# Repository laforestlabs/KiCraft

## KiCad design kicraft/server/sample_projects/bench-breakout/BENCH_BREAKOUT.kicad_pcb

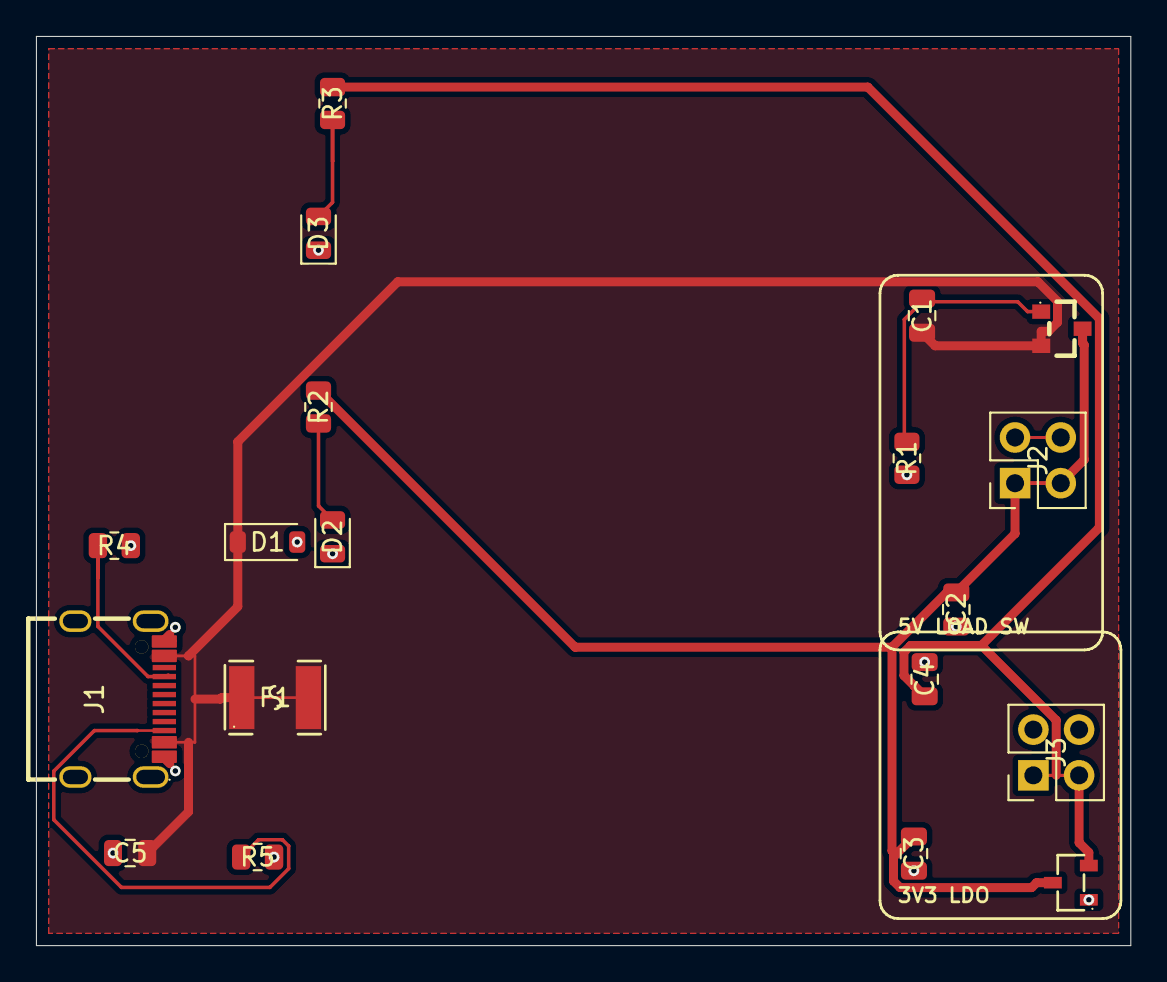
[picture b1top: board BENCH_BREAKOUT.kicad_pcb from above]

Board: 2 copper layers, 60.8 x 50.5 mm, 19 parts (0 on the bottom side), 9 nets.

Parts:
C1: 100nF; C_0805_2012Metric
C2, C5: 10uF; C_0805_2012Metric
C3, C4: 1uF; C_0805_2012Metric
D1: 5V TVS; D_SOD-123
D2: Red; LED_0805_2012Metric
D3: Green; LED_0805_2012Metric
F1: MF-MSMF050-2; F1812
J1: TYPE-C-31-M-12; USB-C_SMD-TYPE-C-31-M-12_1
J2, J3: 2x02 Header; PinHeader_2x02_P2.54mm_Vertical
Q1: AO3401A; SOT-23_L2.9-W1.3-P1.90-LS2.4-BR
R1: 100k; R_0805_2012Metric
R2, R3: 470; R_0805_2012Metric
R4, R5: 5.1k; R_0805_2012Metric
U1: XC6206P332MR; SOT-23-3_L2.9-W1.3-P1.90-LS2.4-BR

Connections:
+3V3: C4.1, J3.1, J3.3, R3.1, U1.2
+5V: C2.1, C3.1, J2.1, J2.3, Q1.3, R2.1, U1.3
CC1: J1.A5, R4.1
CC2: J1.B5, R5.1
GATE: C1.1, Q1.1, R1.1
GND: C2.2, C3.2, C4.2, C5.2, D1.2, D2.1, D3.1, J1.1, J1.2, J1.3, J1.4, J1.A1B12, J1.B1A12, J2.2, J2.4, J3.2, J3.4, R1.2, R4.2, R5.2, U1.1
LED3V3_ANODE: D3.2, R3.2
LED5V_ANODE: D2.2, R2.2
VBUS: C1.2, C5.1, D1.1, F1.1, F1.2, J1.A4B9, J1.B4A9, Q1.2

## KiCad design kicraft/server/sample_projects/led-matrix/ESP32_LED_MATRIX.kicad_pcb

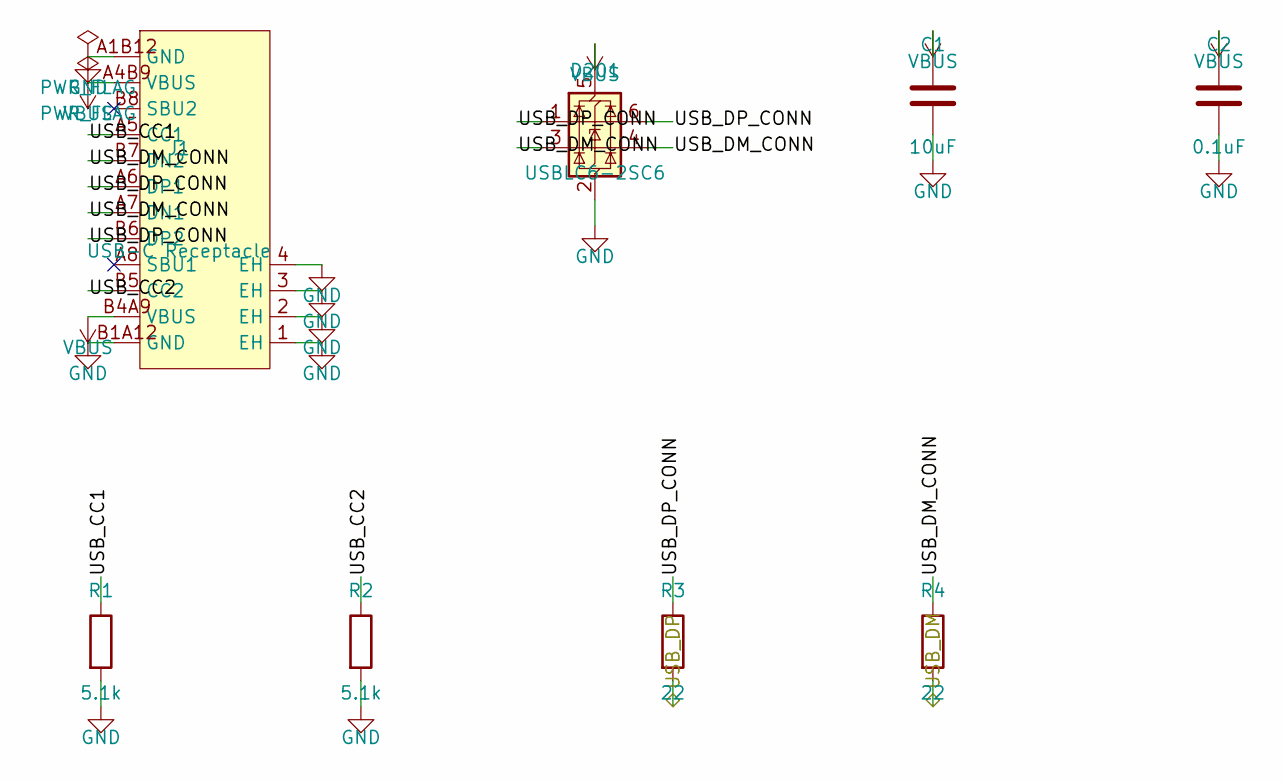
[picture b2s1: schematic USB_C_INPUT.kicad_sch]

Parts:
C1: 10uF; C_0805_2012Metric
C2: 0.1uF; C_0402_1005Metric
D201: USBLC6-2SC6; SOT-23-6
J1: USB-C Receptacle; USB-C_SMD-TYPE-C-31-M-12_1
R1, R2: 5.1k; R_0402_1005Metric
R3, R4: 22; R_0402_1005Metric

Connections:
USB_CC1: J1.A5 (CC1), R1.1
USB_CC2: J1.B5 (CC2), R2.1
USB_DM: R4.2; also elsewhere on the board
USB_DM_CONN: D201.3 (I/O2), D201.4 (I/O2), J1.A7 (DN1), J1.B7 (DN2), R4.1
USB_DP: R3.2; also elsewhere on the board
USB_DP_CONN: D201.1 (I/O1), D201.6 (I/O1), J1.A6 (DP1), J1.B6 (DP2), R3.1

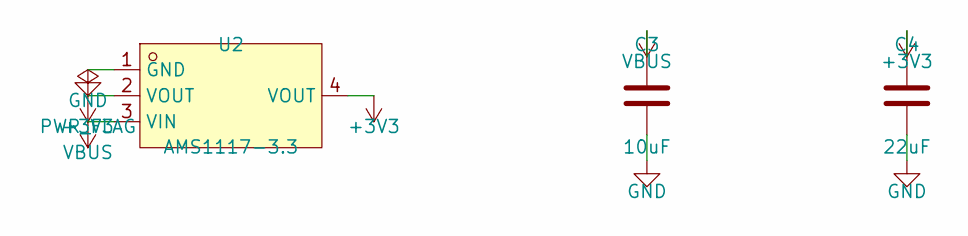
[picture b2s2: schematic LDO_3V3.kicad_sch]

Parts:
C3: 10uF; C_0805_2012Metric
C4: 22uF; C_0805_2012Metric
U2: AMS1117-3.3; SOT-223-3_L6.5-W3.4-P2.30-LS7.0-BR

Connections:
+3V3: C4.1, U2.2 (VOUT), U2.4 (VOUT); also elsewhere on the board

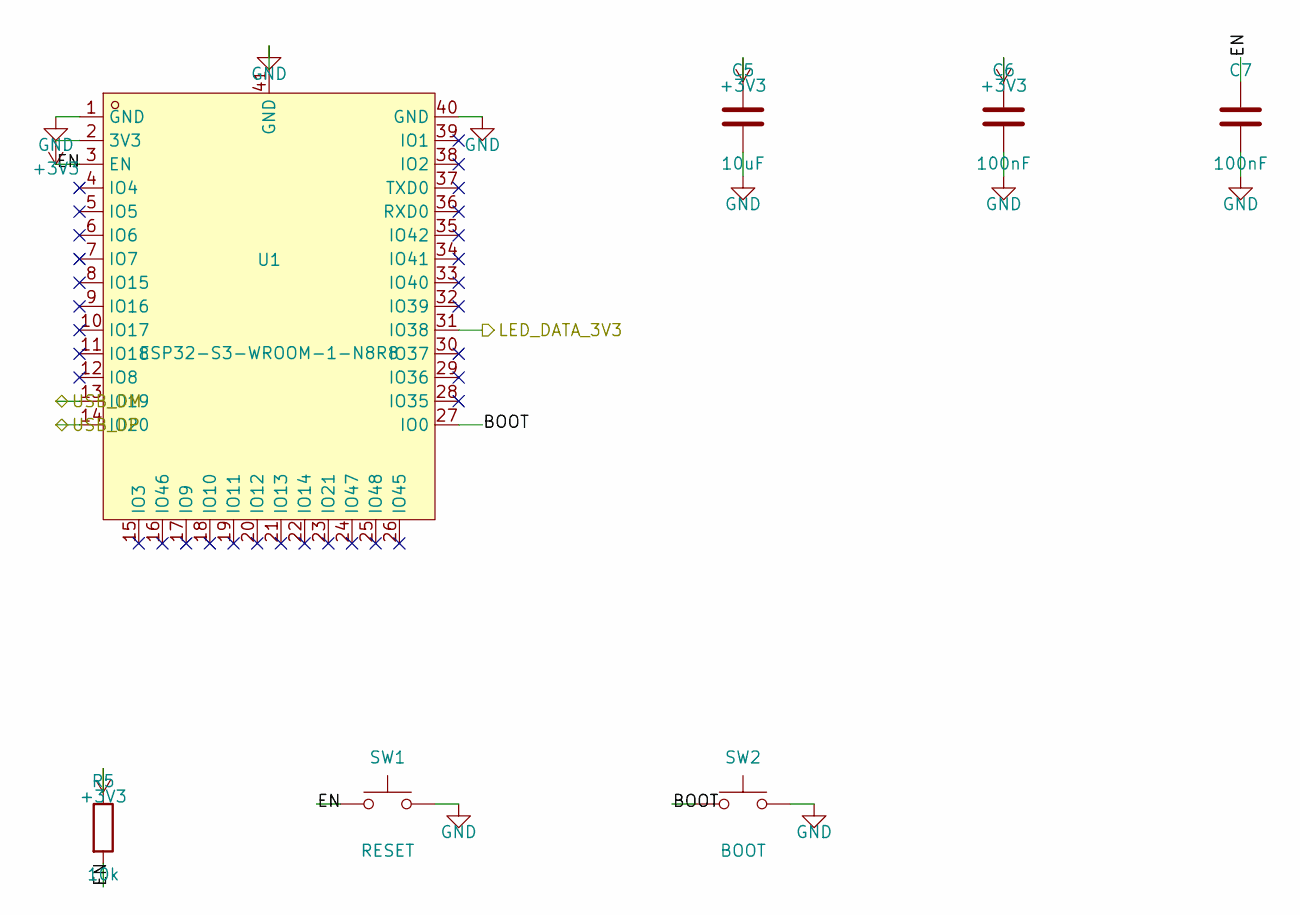
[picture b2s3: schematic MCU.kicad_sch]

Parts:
C5: 10uF; C_0805_2012Metric
C6, C7: 100nF; C_0402_1005Metric
R5: 10k; R_0402_1005Metric
SW1: RESET; SW_Push_1P1T_NO_CK_KMR2
SW2: BOOT; SW_Push_1P1T_NO_CK_KMR2
U1: ESP32-S3-WROOM-1-N8R8; WIRELM-SMD_ESP32-S3-WROOM-1

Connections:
+3V3: C5.1, C6.1, R5.1, U1.2 (3V3); also elsewhere on the board
BOOT: SW2.1, U1.27 (IO0)
EN: C7.1, R5.2, SW1.1, U1.3 (EN)
LED_DATA_3V3: U1.31 (IO38); also elsewhere on the board
USB_DM: U1.13 (IO19); also elsewhere on the board
USB_DP: U1.14 (IO20); also elsewhere on the board

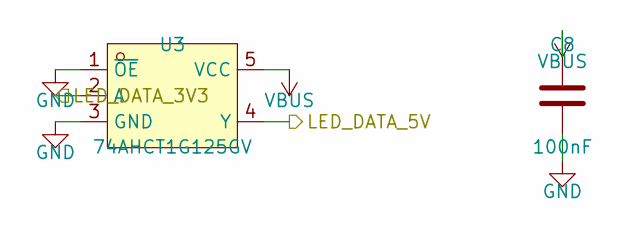
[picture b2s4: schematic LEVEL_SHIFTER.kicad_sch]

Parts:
C8: 100nF; C_0402_1005Metric
U3: 74AHCT1G125GV; SOT-23-5_L3.0-W1.7-P0.95-LS2.8-BL

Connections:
LED_DATA_3V3: U3.2 (A); also elsewhere on the board
LED_DATA_5V: U3.4 (Y); also elsewhere on the board

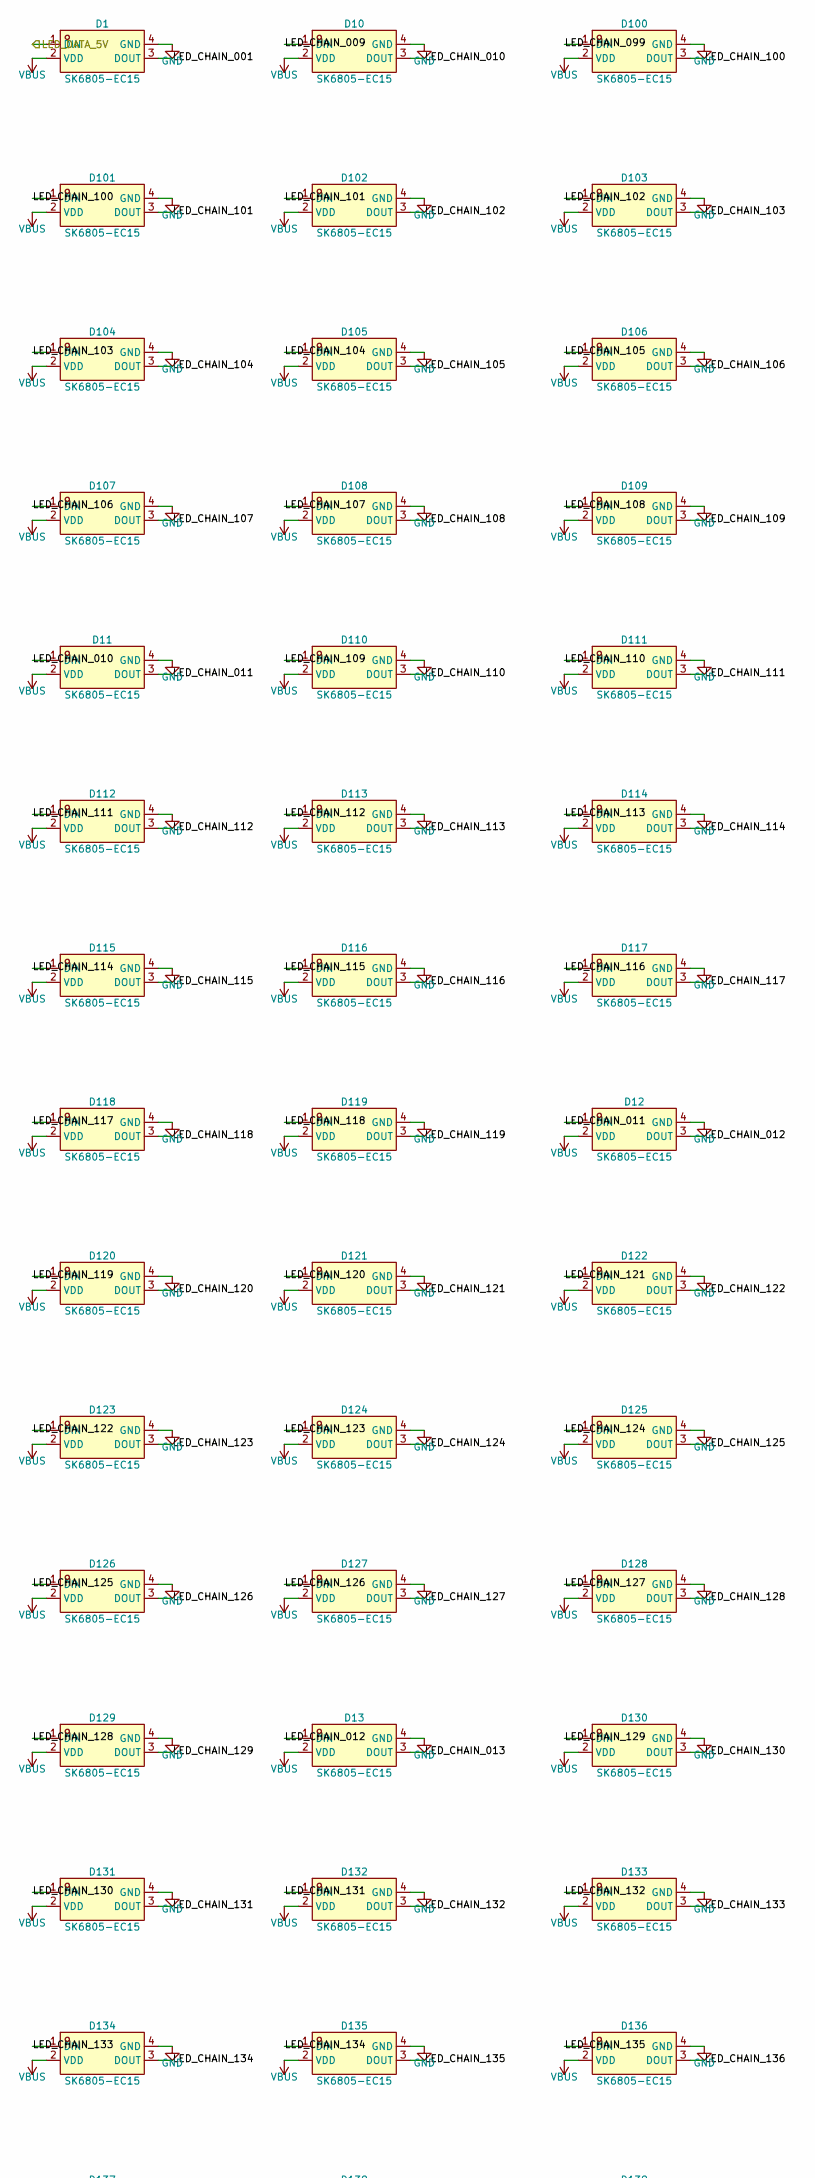
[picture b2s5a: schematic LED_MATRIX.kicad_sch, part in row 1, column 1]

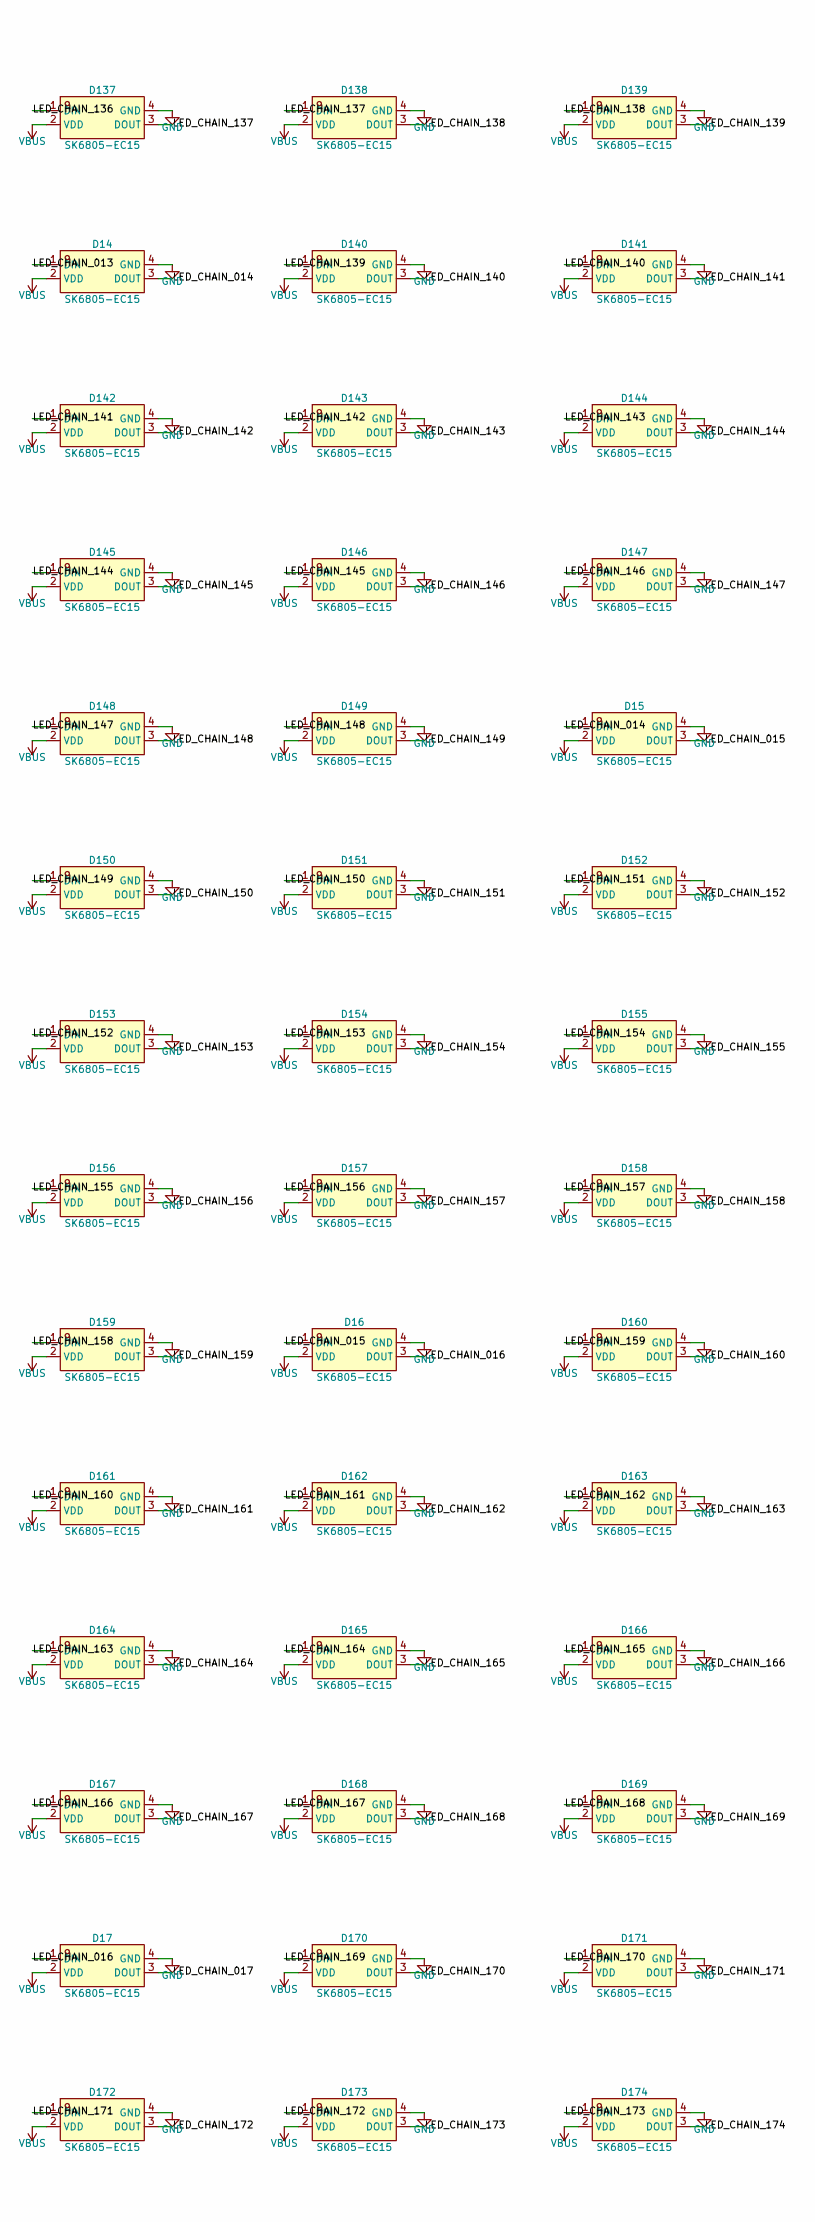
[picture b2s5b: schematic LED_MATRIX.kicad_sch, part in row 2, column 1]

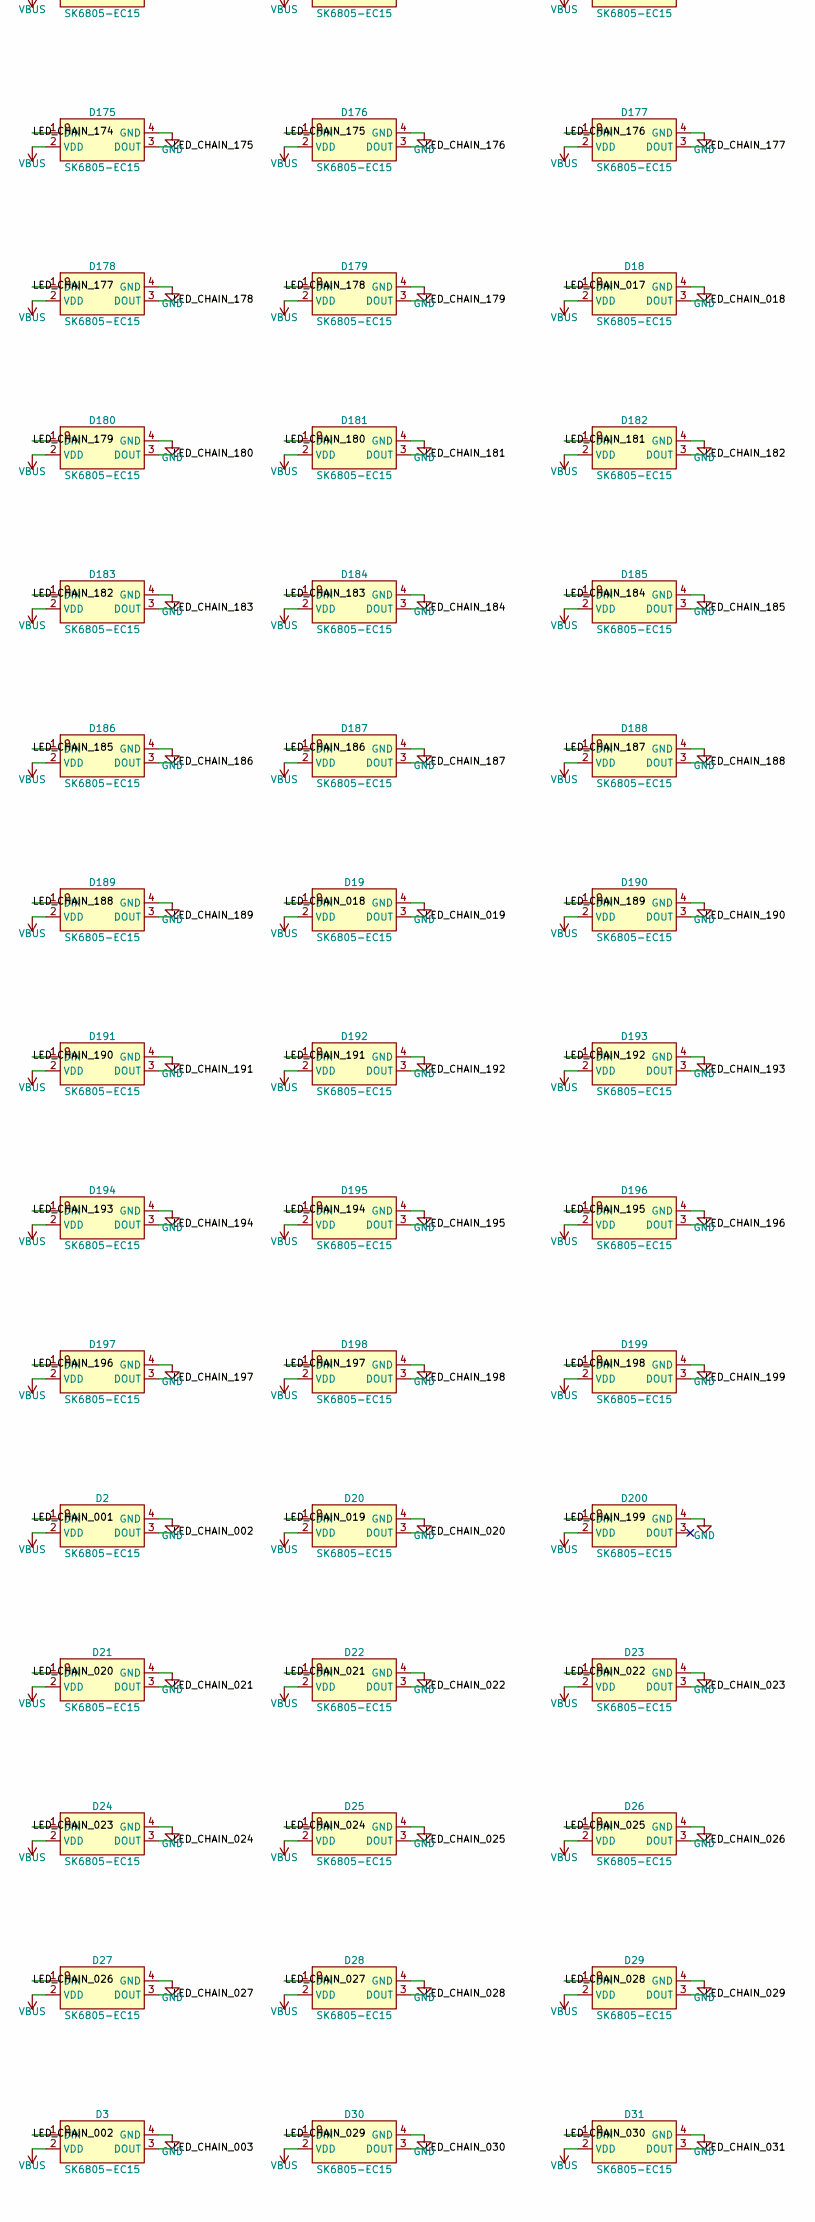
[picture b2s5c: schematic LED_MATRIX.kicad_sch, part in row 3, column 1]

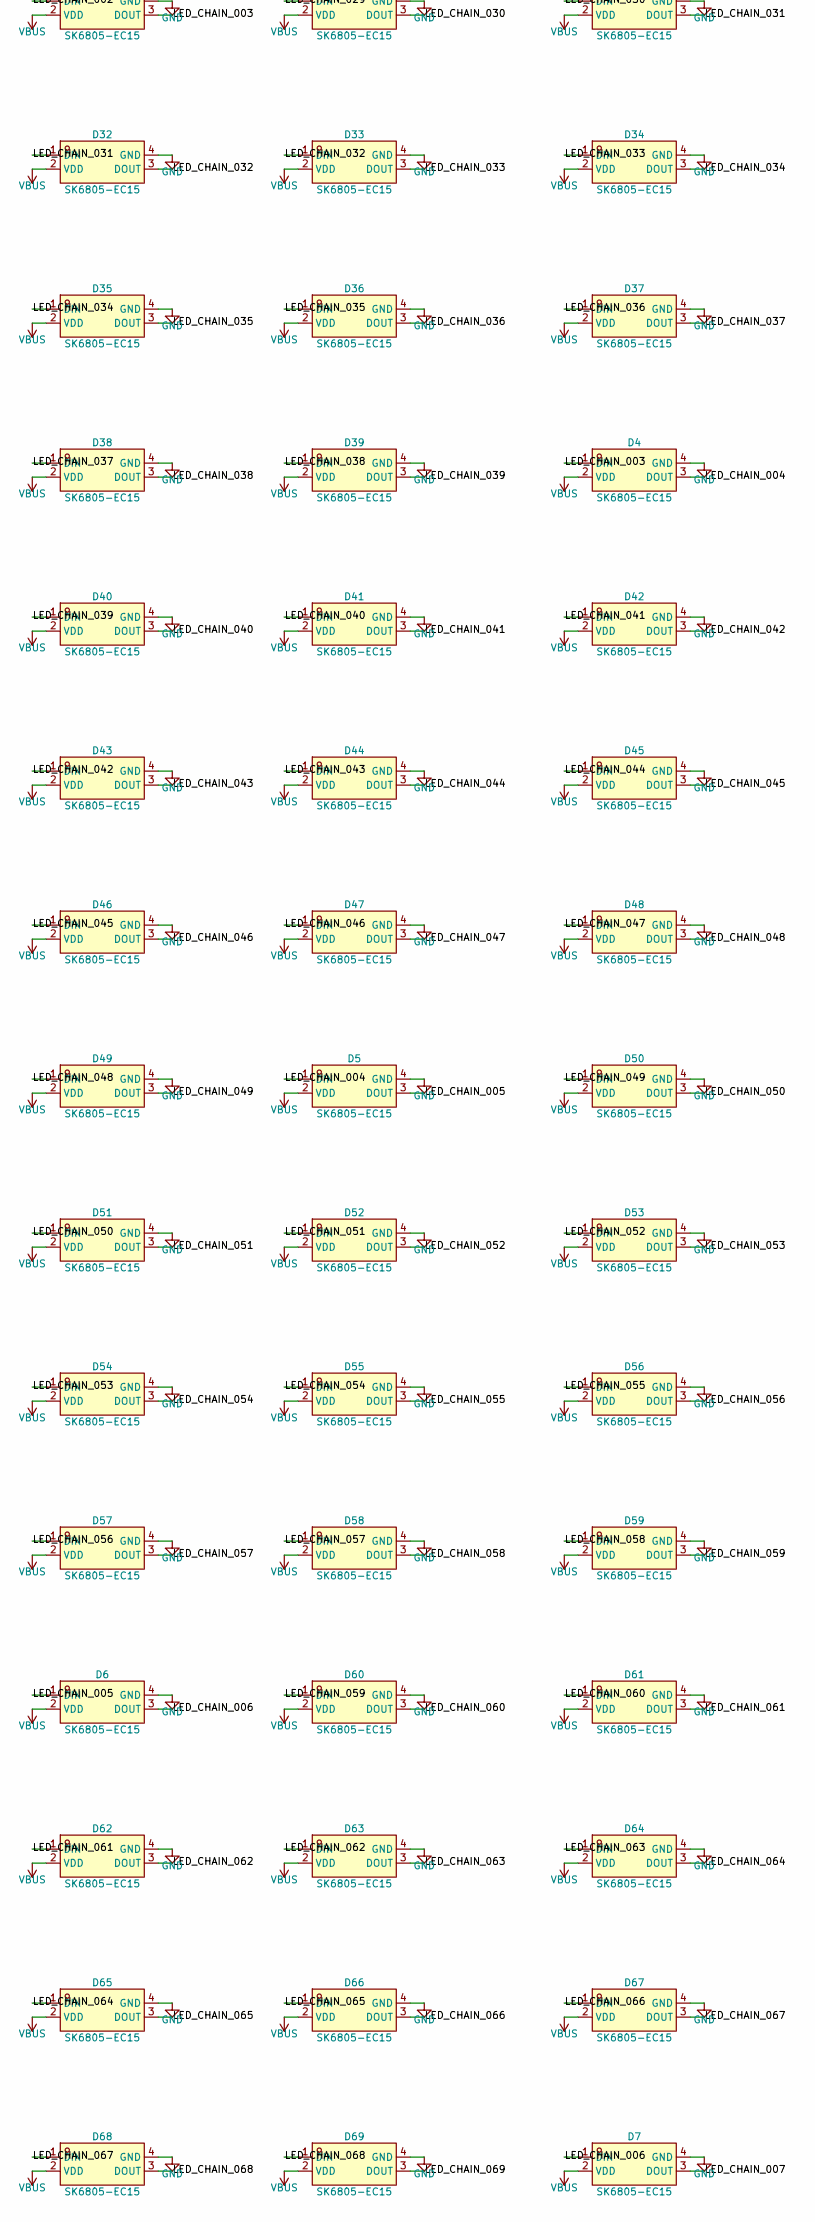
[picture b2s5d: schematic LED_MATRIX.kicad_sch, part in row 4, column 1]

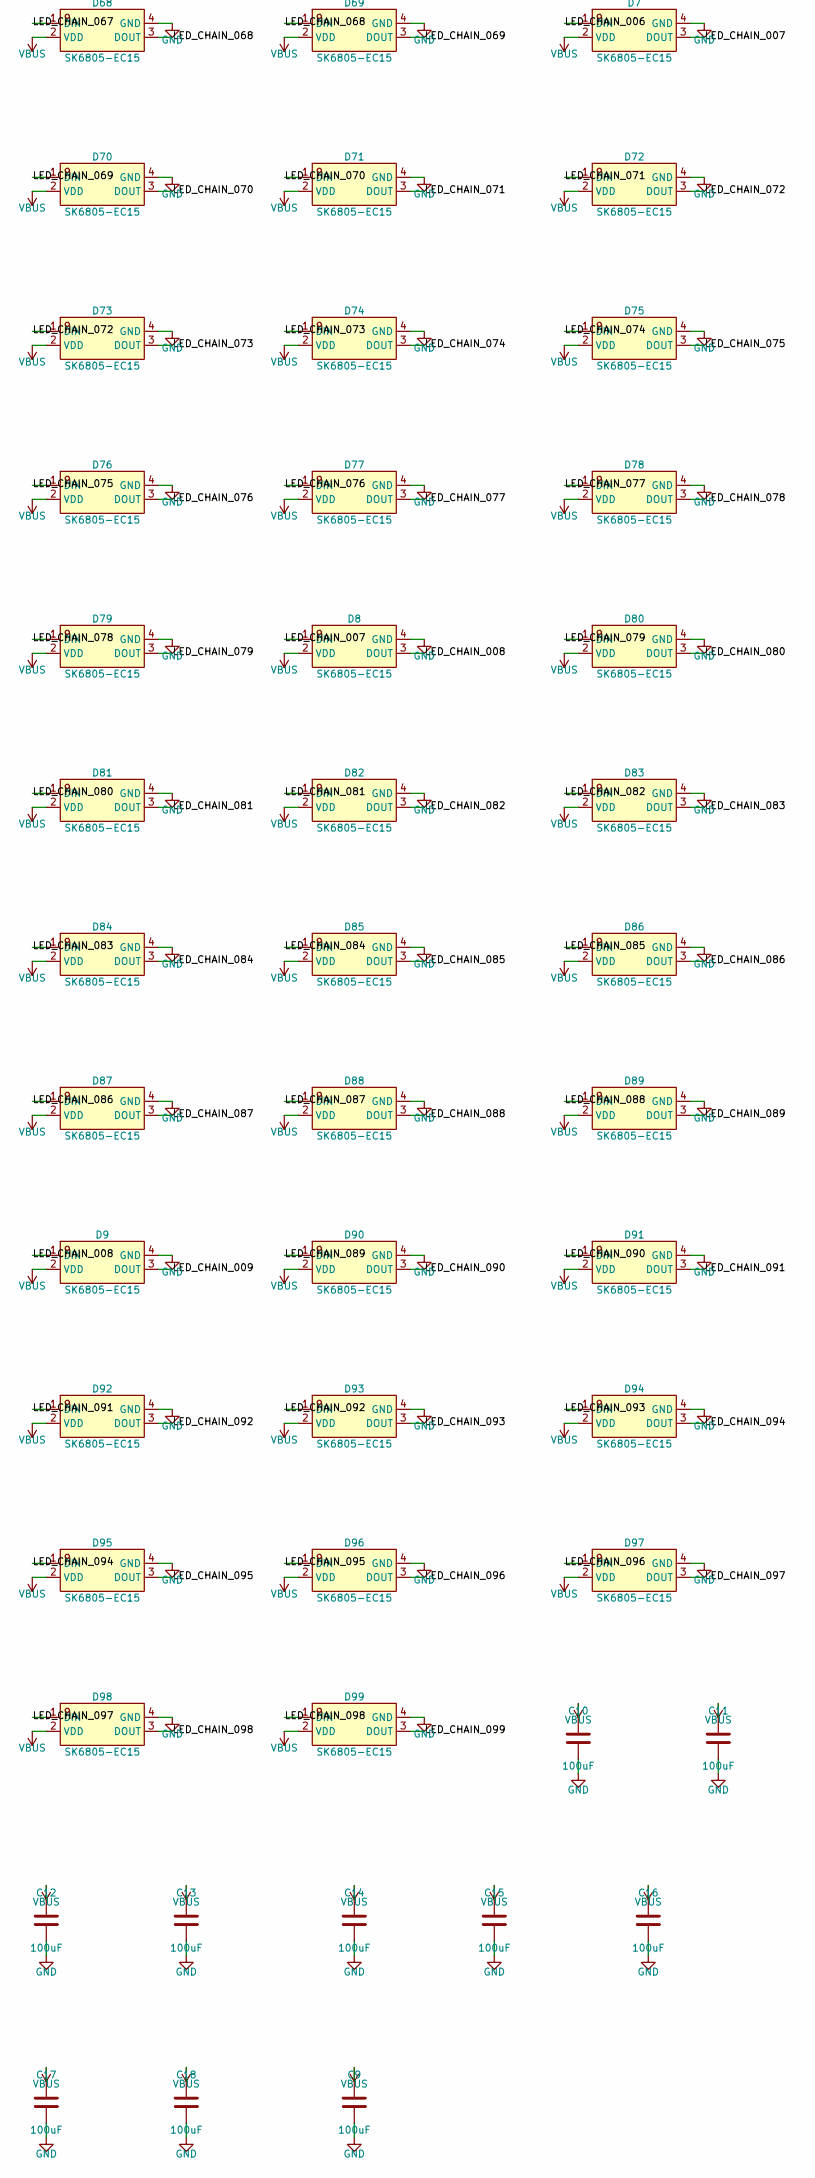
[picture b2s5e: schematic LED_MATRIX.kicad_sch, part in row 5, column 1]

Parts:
C9, C10, C11, C12, C13, C14, C15, C16, C17, C18: 100uF; C_1206_3216Metric
D1, D2, D3, D4, D5, D6, D7, D8, D9, D10, D11, D12, D13, D14, D15, D16, D17, D18, D19, D20, D21, D22, D23, D24, D25, D26, D27, D28, D29, D30, D31, D32, D33, D34, D35, D36, D37, D38, D39, D40, D41, D42, D43, D44, D45, D46, D47, D48, D49, D50, D51, D52, D53, D54, D55, D56, D57, D58, D59, D60, D61, D62, D63, D64, D65, D66, D67, D68, D69, D70, D71, D72, D73, D74, D75, D76, D77, D78, D79, D80, D81, D82, D83, D84, D85, D86, D87, D88, D89, D90, D91, D92, D93, D94, D95, D96, D97, D98, D99, D100, D101, D102, D103, D104, D105, D106, D107, D108, D109, D110, D111, D112, D113, D114, D115, D116, D117, D118, D119, D120, D121, D122, D123, D124, D125, D126, D127, D128, D129, D130, D131, D132, D133, D134, D135, D136, D137, D138, D139, D140, D141, D142, D143, D144, D145, D146, D147, D148, D149, D150, D151, D152, D153, D154, D155, D156, D157, D158, D159, D160, D161, D162, D163, D164, D165, D166, D167, D168, D169, D170, D171, D172, D173, D174, D175, D176, D177, D178, D179, D180, D181, D182, D183, D184, D185, D186, D187, D188, D189, D190, D191, D192, D193, D194, D195, D196, D197, D198, D199, D200: SK6805-EC15; LED-SMD_4P-L1.5-W1.5-BL

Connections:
LED_CHAIN_001: D1.3 (DOUT), D2.1 (DIN)
LED_CHAIN_002: D2.3 (DOUT), D3.1 (DIN)
LED_CHAIN_003: D3.3 (DOUT), D4.1 (DIN)
LED_CHAIN_004: D4.3 (DOUT), D5.1 (DIN)
LED_CHAIN_005: D5.3 (DOUT), D6.1 (DIN)
LED_CHAIN_006: D6.3 (DOUT), D7.1 (DIN)
LED_CHAIN_007: D7.3 (DOUT), D8.1 (DIN)
LED_CHAIN_008: D8.3 (DOUT), D9.1 (DIN)
LED_CHAIN_009: D9.3 (DOUT), D10.1 (DIN)
LED_CHAIN_010: D10.3 (DOUT), D11.1 (DIN)
LED_CHAIN_011: D11.3 (DOUT), D12.1 (DIN)
LED_CHAIN_012: D12.3 (DOUT), D13.1 (DIN)
LED_CHAIN_013: D13.3 (DOUT), D14.1 (DIN)
LED_CHAIN_014: D14.3 (DOUT), D15.1 (DIN)
LED_CHAIN_015: D15.3 (DOUT), D16.1 (DIN)
LED_CHAIN_016: D16.3 (DOUT), D17.1 (DIN)
LED_CHAIN_017: D17.3 (DOUT), D18.1 (DIN)
LED_CHAIN_018: D18.3 (DOUT), D19.1 (DIN)
LED_CHAIN_019: D19.3 (DOUT), D20.1 (DIN)
LED_CHAIN_020: D20.3 (DOUT), D21.1 (DIN)
LED_CHAIN_021: D21.3 (DOUT), D22.1 (DIN)
LED_CHAIN_022: D22.3 (DOUT), D23.1 (DIN)
LED_CHAIN_023: D23.3 (DOUT), D24.1 (DIN)
LED_CHAIN_024: D24.3 (DOUT), D25.1 (DIN)
LED_CHAIN_025: D25.3 (DOUT), D26.1 (DIN)
LED_CHAIN_026: D26.3 (DOUT), D27.1 (DIN)
LED_CHAIN_027: D27.3 (DOUT), D28.1 (DIN)
LED_CHAIN_028: D28.3 (DOUT), D29.1 (DIN)
LED_CHAIN_029: D29.3 (DOUT), D30.1 (DIN)
LED_CHAIN_030: D30.3 (DOUT), D31.1 (DIN)
LED_CHAIN_031: D31.3 (DOUT), D32.1 (DIN)
LED_CHAIN_032: D32.3 (DOUT), D33.1 (DIN)
LED_CHAIN_033: D33.3 (DOUT), D34.1 (DIN)
LED_CHAIN_034: D34.3 (DOUT), D35.1 (DIN)
LED_CHAIN_035: D35.3 (DOUT), D36.1 (DIN)
LED_CHAIN_036: D36.3 (DOUT), D37.1 (DIN)
LED_CHAIN_037: D37.3 (DOUT), D38.1 (DIN)
LED_CHAIN_038: D38.3 (DOUT), D39.1 (DIN)
LED_CHAIN_039: D39.3 (DOUT), D40.1 (DIN)
LED_CHAIN_040: D40.3 (DOUT), D41.1 (DIN)
LED_CHAIN_041: D41.3 (DOUT), D42.1 (DIN)
LED_CHAIN_042: D42.3 (DOUT), D43.1 (DIN)
LED_CHAIN_043: D43.3 (DOUT), D44.1 (DIN)
LED_CHAIN_044: D44.3 (DOUT), D45.1 (DIN)
LED_CHAIN_045: D45.3 (DOUT), D46.1 (DIN)
LED_CHAIN_046: D46.3 (DOUT), D47.1 (DIN)
LED_CHAIN_047: D47.3 (DOUT), D48.1 (DIN)
LED_CHAIN_048: D48.3 (DOUT), D49.1 (DIN)
LED_CHAIN_049: D49.3 (DOUT), D50.1 (DIN)
LED_CHAIN_050: D50.3 (DOUT), D51.1 (DIN)
LED_CHAIN_051: D51.3 (DOUT), D52.1 (DIN)
LED_CHAIN_052: D52.3 (DOUT), D53.1 (DIN)
LED_CHAIN_053: D53.3 (DOUT), D54.1 (DIN)
LED_CHAIN_054: D54.3 (DOUT), D55.1 (DIN)
LED_CHAIN_055: D55.3 (DOUT), D56.1 (DIN)
LED_CHAIN_056: D56.3 (DOUT), D57.1 (DIN)
LED_CHAIN_057: D57.3 (DOUT), D58.1 (DIN)
LED_CHAIN_058: D58.3 (DOUT), D59.1 (DIN)
LED_CHAIN_059: D59.3 (DOUT), D60.1 (DIN)
LED_CHAIN_060: D60.3 (DOUT), D61.1 (DIN)
LED_CHAIN_061: D61.3 (DOUT), D62.1 (DIN)
LED_CHAIN_062: D62.3 (DOUT), D63.1 (DIN)
LED_CHAIN_063: D63.3 (DOUT), D64.1 (DIN)
LED_CHAIN_064: D64.3 (DOUT), D65.1 (DIN)
LED_CHAIN_065: D65.3 (DOUT), D66.1 (DIN)
LED_CHAIN_066: D66.3 (DOUT), D67.1 (DIN)
LED_CHAIN_067: D67.3 (DOUT), D68.1 (DIN)
LED_CHAIN_068: D68.3 (DOUT), D69.1 (DIN)
LED_CHAIN_069: D69.3 (DOUT), D70.1 (DIN)
LED_CHAIN_070: D70.3 (DOUT), D71.1 (DIN)
LED_CHAIN_071: D71.3 (DOUT), D72.1 (DIN)
LED_CHAIN_072: D72.3 (DOUT), D73.1 (DIN)
LED_CHAIN_073: D73.3 (DOUT), D74.1 (DIN)
LED_CHAIN_074: D74.3 (DOUT), D75.1 (DIN)
LED_CHAIN_075: D75.3 (DOUT), D76.1 (DIN)
LED_CHAIN_076: D76.3 (DOUT), D77.1 (DIN)
LED_CHAIN_077: D77.3 (DOUT), D78.1 (DIN)
LED_CHAIN_078: D78.3 (DOUT), D79.1 (DIN)
LED_CHAIN_079: D79.3 (DOUT), D80.1 (DIN)
LED_CHAIN_080: D80.3 (DOUT), D81.1 (DIN)
LED_CHAIN_081: D81.3 (DOUT), D82.1 (DIN)
LED_CHAIN_082: D82.3 (DOUT), D83.1 (DIN)
LED_CHAIN_083: D83.3 (DOUT), D84.1 (DIN)
LED_CHAIN_084: D84.3 (DOUT), D85.1 (DIN)
LED_CHAIN_085: D85.3 (DOUT), D86.1 (DIN)
LED_CHAIN_086: D86.3 (DOUT), D87.1 (DIN)
LED_CHAIN_087: D87.3 (DOUT), D88.1 (DIN)
LED_CHAIN_088: D88.3 (DOUT), D89.1 (DIN)
LED_CHAIN_089: D89.3 (DOUT), D90.1 (DIN)
LED_CHAIN_090: D90.3 (DOUT), D91.1 (DIN)
LED_CHAIN_091: D91.3 (DOUT), D92.1 (DIN)
LED_CHAIN_092: D92.3 (DOUT), D93.1 (DIN)
LED_CHAIN_093: D93.3 (DOUT), D94.1 (DIN)
LED_CHAIN_094: D94.3 (DOUT), D95.1 (DIN)
LED_CHAIN_095: D95.3 (DOUT), D96.1 (DIN)
LED_CHAIN_096: D96.3 (DOUT), D97.1 (DIN)
LED_CHAIN_097: D97.3 (DOUT), D98.1 (DIN)
LED_CHAIN_098: D98.3 (DOUT), D99.1 (DIN)
LED_CHAIN_099: D99.3 (DOUT), D100.1 (DIN)
LED_CHAIN_100: D100.3 (DOUT), D101.1 (DIN)
LED_CHAIN_101: D101.3 (DOUT), D102.1 (DIN)
LED_CHAIN_102: D102.3 (DOUT), D103.1 (DIN)
LED_CHAIN_103: D103.3 (DOUT), D104.1 (DIN)
LED_CHAIN_104: D104.3 (DOUT), D105.1 (DIN)
LED_CHAIN_105: D105.3 (DOUT), D106.1 (DIN)
LED_CHAIN_106: D106.3 (DOUT), D107.1 (DIN)
LED_CHAIN_107: D107.3 (DOUT), D108.1 (DIN)
LED_CHAIN_108: D108.3 (DOUT), D109.1 (DIN)
LED_CHAIN_109: D109.3 (DOUT), D110.1 (DIN)
LED_CHAIN_110: D110.3 (DOUT), D111.1 (DIN)
LED_CHAIN_111: D111.3 (DOUT), D112.1 (DIN)
LED_CHAIN_112: D112.3 (DOUT), D113.1 (DIN)
LED_CHAIN_113: D113.3 (DOUT), D114.1 (DIN)
LED_CHAIN_114: D114.3 (DOUT), D115.1 (DIN)
LED_CHAIN_115: D115.3 (DOUT), D116.1 (DIN)
LED_CHAIN_116: D116.3 (DOUT), D117.1 (DIN)
LED_CHAIN_117: D117.3 (DOUT), D118.1 (DIN)
LED_CHAIN_118: D118.3 (DOUT), D119.1 (DIN)
LED_CHAIN_119: D119.3 (DOUT), D120.1 (DIN)
LED_CHAIN_120: D120.3 (DOUT), D121.1 (DIN)
LED_CHAIN_121: D121.3 (DOUT), D122.1 (DIN)
LED_CHAIN_122: D122.3 (DOUT), D123.1 (DIN)
LED_CHAIN_123: D123.3 (DOUT), D124.1 (DIN)
LED_CHAIN_124: D124.3 (DOUT), D125.1 (DIN)
LED_CHAIN_125: D125.3 (DOUT), D126.1 (DIN)
LED_CHAIN_126: D126.3 (DOUT), D127.1 (DIN)
LED_CHAIN_127: D127.3 (DOUT), D128.1 (DIN)
LED_CHAIN_128: D128.3 (DOUT), D129.1 (DIN)
LED_CHAIN_129: D129.3 (DOUT), D130.1 (DIN)
LED_CHAIN_130: D130.3 (DOUT), D131.1 (DIN)
LED_CHAIN_131: D131.3 (DOUT), D132.1 (DIN)
LED_CHAIN_132: D132.3 (DOUT), D133.1 (DIN)
LED_CHAIN_133: D133.3 (DOUT), D134.1 (DIN)
LED_CHAIN_134: D134.3 (DOUT), D135.1 (DIN)
LED_CHAIN_135: D135.3 (DOUT), D136.1 (DIN)
LED_CHAIN_136: D136.3 (DOUT), D137.1 (DIN)
LED_CHAIN_137: D137.3 (DOUT), D138.1 (DIN)
LED_CHAIN_138: D138.3 (DOUT), D139.1 (DIN)
LED_CHAIN_139: D139.3 (DOUT), D140.1 (DIN)
LED_CHAIN_140: D140.3 (DOUT), D141.1 (DIN)
LED_CHAIN_141: D141.3 (DOUT), D142.1 (DIN)
LED_CHAIN_142: D142.3 (DOUT), D143.1 (DIN)
LED_CHAIN_143: D143.3 (DOUT), D144.1 (DIN)
LED_CHAIN_144: D144.3 (DOUT), D145.1 (DIN)
LED_CHAIN_145: D145.3 (DOUT), D146.1 (DIN)
LED_CHAIN_146: D146.3 (DOUT), D147.1 (DIN)
LED_CHAIN_147: D147.3 (DOUT), D148.1 (DIN)
LED_CHAIN_148: D148.3 (DOUT), D149.1 (DIN)
LED_CHAIN_149: D149.3 (DOUT), D150.1 (DIN)
LED_CHAIN_150: D150.3 (DOUT), D151.1 (DIN)
LED_CHAIN_151: D151.3 (DOUT), D152.1 (DIN)
LED_CHAIN_152: D152.3 (DOUT), D153.1 (DIN)
LED_CHAIN_153: D153.3 (DOUT), D154.1 (DIN)
LED_CHAIN_154: D154.3 (DOUT), D155.1 (DIN)
LED_CHAIN_155: D155.3 (DOUT), D156.1 (DIN)
LED_CHAIN_156: D156.3 (DOUT), D157.1 (DIN)
LED_CHAIN_157: D157.3 (DOUT), D158.1 (DIN)
LED_CHAIN_158: D158.3 (DOUT), D159.1 (DIN)
LED_CHAIN_159: D159.3 (DOUT), D160.1 (DIN)
LED_CHAIN_160: D160.3 (DOUT), D161.1 (DIN)
LED_CHAIN_161: D161.3 (DOUT), D162.1 (DIN)
LED_CHAIN_162: D162.3 (DOUT), D163.1 (DIN)
LED_CHAIN_163: D163.3 (DOUT), D164.1 (DIN)
LED_CHAIN_164: D164.3 (DOUT), D165.1 (DIN)
LED_CHAIN_165: D165.3 (DOUT), D166.1 (DIN)
LED_CHAIN_166: D166.3 (DOUT), D167.1 (DIN)
LED_CHAIN_167: D167.3 (DOUT), D168.1 (DIN)
LED_CHAIN_168: D168.3 (DOUT), D169.1 (DIN)
LED_CHAIN_169: D169.3 (DOUT), D170.1 (DIN)
LED_CHAIN_170: D170.3 (DOUT), D171.1 (DIN)
LED_CHAIN_171: D171.3 (DOUT), D172.1 (DIN)
LED_CHAIN_172: D172.3 (DOUT), D173.1 (DIN)
LED_CHAIN_173: D173.3 (DOUT), D174.1 (DIN)
LED_CHAIN_174: D174.3 (DOUT), D175.1 (DIN)
LED_CHAIN_175: D175.3 (DOUT), D176.1 (DIN)
LED_CHAIN_176: D176.3 (DOUT), D177.1 (DIN)
LED_CHAIN_177: D177.3 (DOUT), D178.1 (DIN)
LED_CHAIN_178: D178.3 (DOUT), D179.1 (DIN)
LED_CHAIN_179: D179.3 (DOUT), D180.1 (DIN)
LED_CHAIN_180: D180.3 (DOUT), D181.1 (DIN)
LED_CHAIN_181: D181.3 (DOUT), D182.1 (DIN)
LED_CHAIN_182: D182.3 (DOUT), D183.1 (DIN)
LED_CHAIN_183: D183.3 (DOUT), D184.1 (DIN)
LED_CHAIN_184: D184.3 (DOUT), D185.1 (DIN)
LED_CHAIN_185: D185.3 (DOUT), D186.1 (DIN)
LED_CHAIN_186: D186.3 (DOUT), D187.1 (DIN)
LED_CHAIN_187: D187.3 (DOUT), D188.1 (DIN)
LED_CHAIN_188: D188.3 (DOUT), D189.1 (DIN)
LED_CHAIN_189: D189.3 (DOUT), D190.1 (DIN)
LED_CHAIN_190: D190.3 (DOUT), D191.1 (DIN)
LED_CHAIN_191: D191.3 (DOUT), D192.1 (DIN)
LED_CHAIN_192: D192.3 (DOUT), D193.1 (DIN)
LED_CHAIN_193: D193.3 (DOUT), D194.1 (DIN)
LED_CHAIN_194: D194.3 (DOUT), D195.1 (DIN)
LED_CHAIN_195: D195.3 (DOUT), D196.1 (DIN)
LED_CHAIN_196: D196.3 (DOUT), D197.1 (DIN)
LED_CHAIN_197: D197.3 (DOUT), D198.1 (DIN)
LED_CHAIN_198: D198.3 (DOUT), D199.1 (DIN)
LED_CHAIN_199: D199.3 (DOUT), D200.1 (DIN)
LED_DATA_5V: D1.1 (DIN); also elsewhere on the board

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
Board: 2 copper layers, 230 parts (0 on the bottom side), 212 nets, no tracks yet.

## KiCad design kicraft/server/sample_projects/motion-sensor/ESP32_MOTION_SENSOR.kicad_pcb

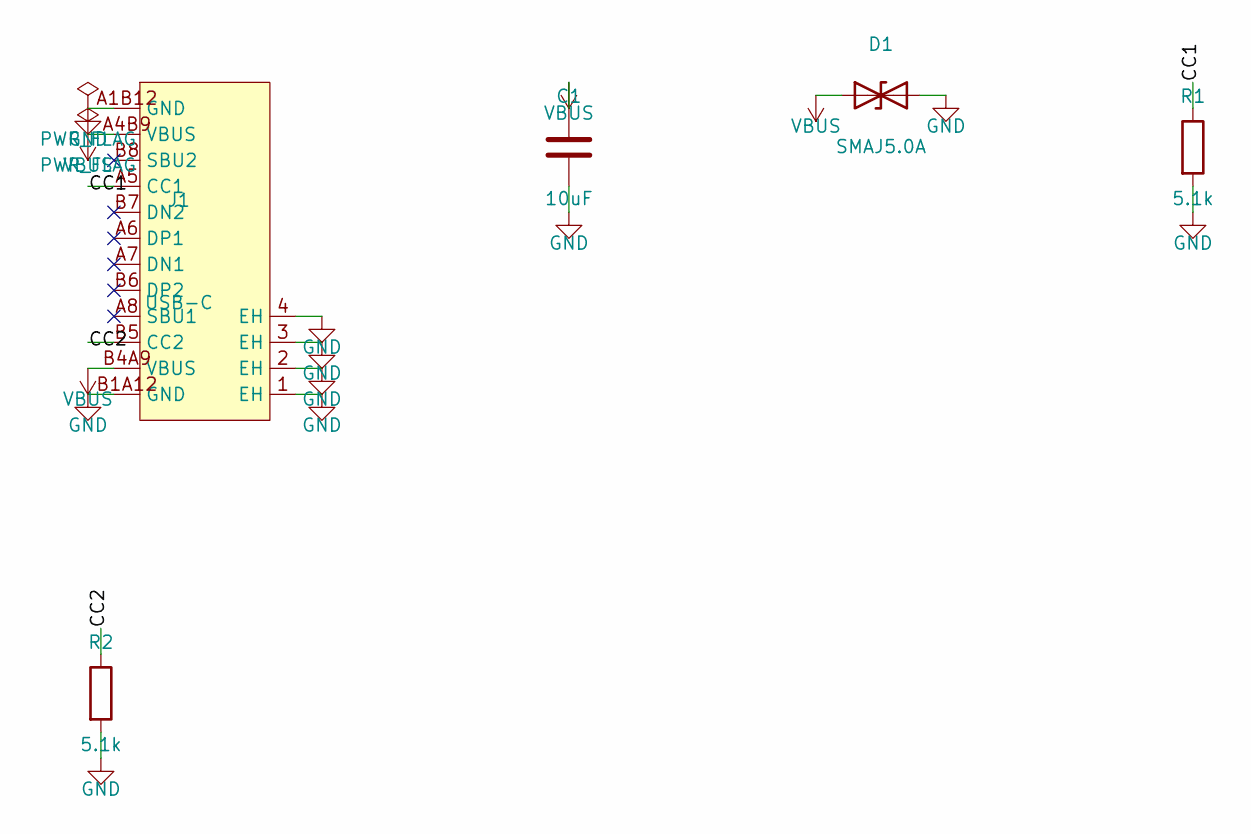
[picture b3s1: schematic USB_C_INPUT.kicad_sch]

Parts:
C1: 10uF; C_0805_2012Metric
D1: SMAJ5.0A; D_SMA
J1: USB-C; USB-C_SMD-TYPE-C-31-M-12_1
R1, R2: 5.1k; R_0603_1608Metric

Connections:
CC1: J1.A5 (CC1), R1.1
CC2: J1.B5 (CC2), R2.1

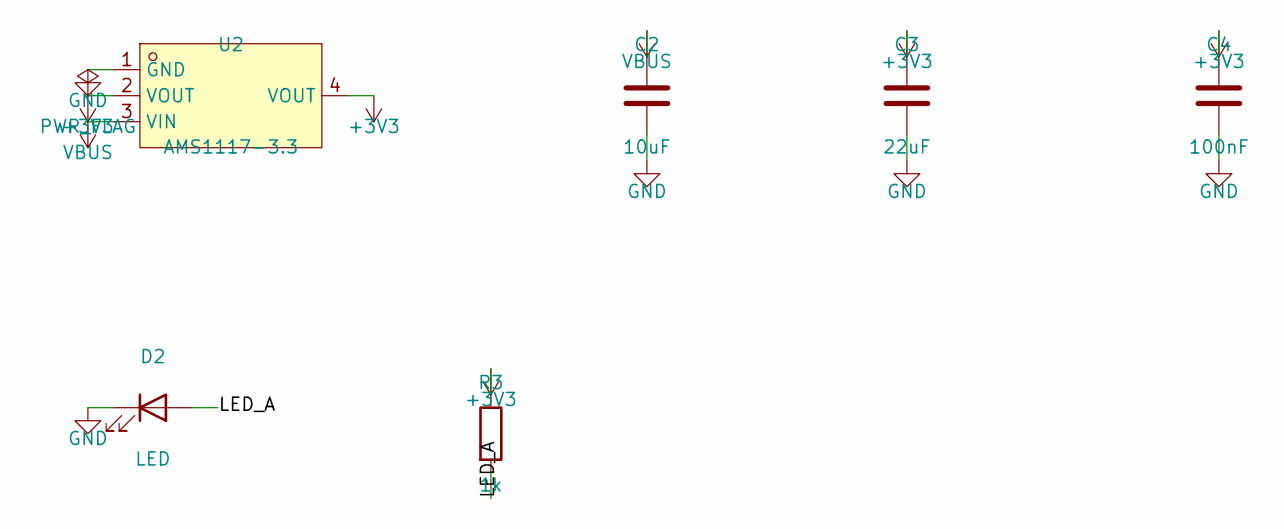
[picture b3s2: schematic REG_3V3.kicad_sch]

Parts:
C2: 10uF; C_0805_2012Metric
C3: 22uF; C_0805_2012Metric
C4: 100nF; C_0603_1608Metric
D2: LED; LED_0603_1608Metric
R3: 1k; R_0603_1608Metric
U2: AMS1117-3.3; SOT-223-3_L6.5-W3.4-P2.30-LS7.0-BR

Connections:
+3V3: C3.1, C4.1, R3.1, U2.2 (VOUT), U2.4 (VOUT); also elsewhere on the board
LED_A: D2.2 (A), R3.2
